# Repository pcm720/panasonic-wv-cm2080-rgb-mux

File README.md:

# Panasonic WV-CM1480/1780/2080 RGB Mux

The TV only has two composite inputs and one S-Video input, but can be relatively easily modded for RGB while keeping the other two inputs functional.

The regular RGB mux method cannot be used on these TVs because
- The AN5192K jungle IC doesn’t have dedicated RGB inputs and expects a non-standard input signal up to 2.5V on its OSD RGB lines
- The OSD input uses a single microprocessor output (OSD B out) that's wired to all three RGB inputs (R, G, B) via a buffer transistor

Thus, to add RGB to these TVs, we'll have to amplify the signal to get it to the levels the jungle expects.  
The schematics for WV-CM??80 and other TVs using this jungle ICs suggest that the maximum RGB input level should be somewhere in the 1.4-1.5V range, judging by the voltage divider resistor values used, also confirmed with an oscilloscope.

To amplify the input, we can use THS7314 6 dB 3-channel amplifier.  
It adds a 145 mV shift to the input signal, so the resulting output levels should be somewhere in the ~0.3-1.7V range.  
THS7315 would probably a better choice as it produces ~5V output signal for a 0.7Vp-p input signal (easily divided to the required level), but THS7314 is what I had at hand and seems to work pretty well.

## Installation

The [PCB](pcb/) is designed to be placed on top of AN5192K, with BL, R, G, B, 5V and GND positions matching the actual AN5192K pins to make installation easier.  
It also includes diodes D5-D7 on board, making the installation cleaner.

- Big RGB pads — RGB inputs (bottom pad of each pair is GND)
- BL — blanking output (AN5192K pin 10)
- R — R output (AN5192K pin 11)
- G — G output (AN5192K pin 12)
- B — B output (AN5192K pin 13)
- OSD R — microprocessor OSD input (AN5192K pin 11)
- OSD G — microprocessor OSD input (AN5192K pin 12)
- OSD B — microprocessor OSD input (AN5192K pin 13)
- 5V — 5V (AN5192K pin 23)
- GND — GND (AN5192K pin 26)
- A/B — microprocessor A/B input (R354)
- V/S — microprocessor V/S input (R355)

On WV-CM??80, OSD R, G and B can be bridged together as only the blue output of the microprocessor is used to draw the OSD.

Pictures of the tested installation based on a prototyping PCB are provided [here](pics/).

### The modifications required to the CRT

- Replace the jumper link [J378](pics/j378.jpg) with a 1N4148 diode (D8) to prevent backfeeding our blanking output into the microprocessor.  
  The voltage drop introduced by the 1N4148 diode is negligible as the minimum voltage level AN5192K requires for enabling the RGB input is 1.8V
- [Disconnect](pics/rgb2.jpg) AN5192K pins 11, 12 and 13 from the circuit by desoldering or cutting the chip legs.  
  Add 1N4148 diodes (D5-D7) between each of the pins and OSD output to prevent backfeeding our amplified signals into the original circuit.
- Replace [R208](pics/r208.jpg) (330 Ohm) resistor with a 560 Ohm resistor to compensate for the voltage drop.

### Amplifier

The amplifier circuit is fairly simple and consists of:
- 75 Ohm termination resistors (R1-R3) between RGB input and ground
- 0.1uF capacitors (C1-C3) between RGB inputs and THS7314 inputs to decouple the input
- 100 Ohm resistors (R4-R6) between THS7314 outputs and 1N1418 diodes to limit the output current
- 1N1418 diodes (D1-D3) for each of the three output channels to protect THS7314 outputs from microprocessor output

The voltage drop introduced by the 1N1418 diodes ensures that the RGB inputs receive ~1.2-1.4V, keeping the OSD visible.

### Blanking

Thankfully, Panasonic has used two microprocessor 5V outputs called A/B and V/S to directly control the input switches.  
Thus, we can simply use an AND gate to apply blanking only when the video input A is selected, keeping S-Video and the other composite input functional.

The gate inputs should be connected to A/B and V/S outputs of the microprocessor, after the 1k Ohm resistors [R354 and R355](pics/r354.jpg).  
The gate output should be connected to the jungle IC pin 10 via a current-limiting 330 Ohm resistor (R7) and a 1N4148 diode (D4) to protect the gate output from the microprocessor output.

## Results

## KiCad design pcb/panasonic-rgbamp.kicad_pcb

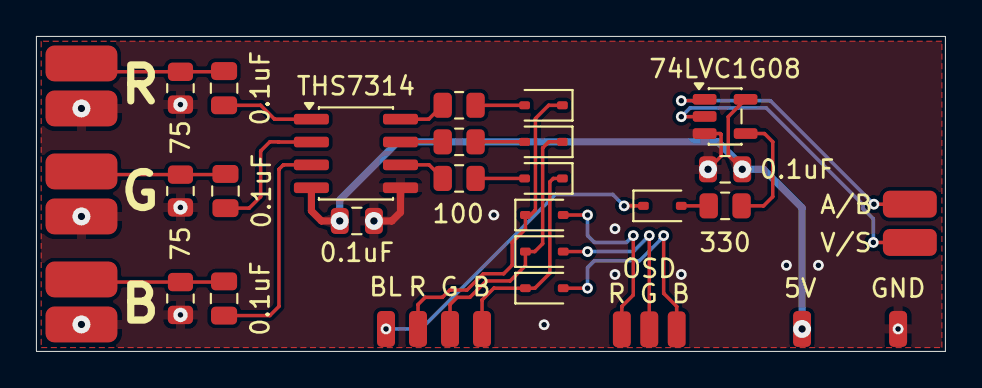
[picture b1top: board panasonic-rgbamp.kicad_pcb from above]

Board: 2 copper layers, 50.5 x 17.5 mm, 38 parts (0 on the bottom side), 25 nets.

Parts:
C1, C2, C3, C4, C5: 0.1uF; C_0805_2012Metric
D1, D2, D3, D4, D5, D6, D7: 1N4148WS; D_SOD-323
J1: R_IN; SolderWirePad_1x01_SMD_2x4mm
J2: R_GND; SolderWirePad_1x01_SMD_2x4mm
J3: G_IN; SolderWirePad_1x01_SMD_2x4mm
J4: G_GND; SolderWirePad_1x01_SMD_2x4mm
J5: B_IN; SolderWirePad_1x01_SMD_2x4mm
J6: B_GND; SolderWirePad_1x01_SMD_2x4mm
J7: OSD_B_IN; SolderWirePad_1x01_SMD_1x2mm
J8: R_OUT; SolderWirePad_1x01_SMD_1x2mm
J9: G_OUT; SolderWirePad_1x01_SMD_1x2mm
J10: B_OUT; SolderWirePad_1x01_SMD_1x2mm
J11: 5V; SolderWirePad_1x01_SMD_1x2mm
J12: GND; SolderWirePad_1x01_SMD_1x2mm
J13: AB_IN; SolderWirePad_1x01_SMD_1.5x3mm
J14: VS_IN; SolderWirePad_1x01_SMD_1.5x3mm
J15: BL_OUT; SolderWirePad_1x01_SMD_1x2mm
J16: OSD_R_IN; SolderWirePad_1x01_SMD_1x2mm
J17: OSD_G_IN; SolderWirePad_1x01_SMD_1x2mm
R1, R2, R3: 75; R_0805_2012Metric
R4, R5, R6: 100; R_0805_2012Metric
R7: 330; R_0805_2012Metric
U1: THS7314; SOIC-8_3.9x4.9mm_P1.27mm
U2: 74LVC1G08; SOT-23-5

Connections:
+5V: C4.2, C5.2, J11.1, U1.4 (Vs), U2.5 (VCC)
A/B IN: J13.1, U2.1
B IN: C3.1, J5.1, R3.1
B OUT: D3.2 (A), R6.2
EXT B IN: D3.1 (K), D7.1 (K), J10.1
EXT BL IN: D4.1 (K), J15.1
EXT G IN: D2.1 (K), D6.1 (K), J9.1
EXT R IN: D1.1 (K), D5.1 (K), J8.1
G IN: C2.1, J3.1, R2.1
G OUT: D2.2 (A), R5.2
GND: C4.1, C5.1, J2.1, J4.1, J6.1, J12.1, R1.2, R2.2, R3.2, U1.5 (GND), U2.3 (GND)
unnamed: D4.2 (A), R7.2
unnamed: R7.1, U2.4
unnamed: C1.2, U1.1 (CH.1_IN)
unnamed: R4.1, U1.8 (CH.1_OUT)
unnamed: C2.2, U1.2 (CH.2_IN)
unnamed: R5.1, U1.7 (CH.2_OUT)
unnamed: C3.2, U1.3 (CH.3_IN)
unnamed: R6.1, U1.6 (CH.3_OUT)
OSD_B_IN: D7.2 (A), J17.1
OSD_G_IN: D6.2 (A), J7.1
OSD_R_IN: D5.2 (A), J16.1
R IN: C1.1, J1.1, R1.1
R OUT: D1.2 (A), R4.2
V/S IN: J14.1, U2.2
